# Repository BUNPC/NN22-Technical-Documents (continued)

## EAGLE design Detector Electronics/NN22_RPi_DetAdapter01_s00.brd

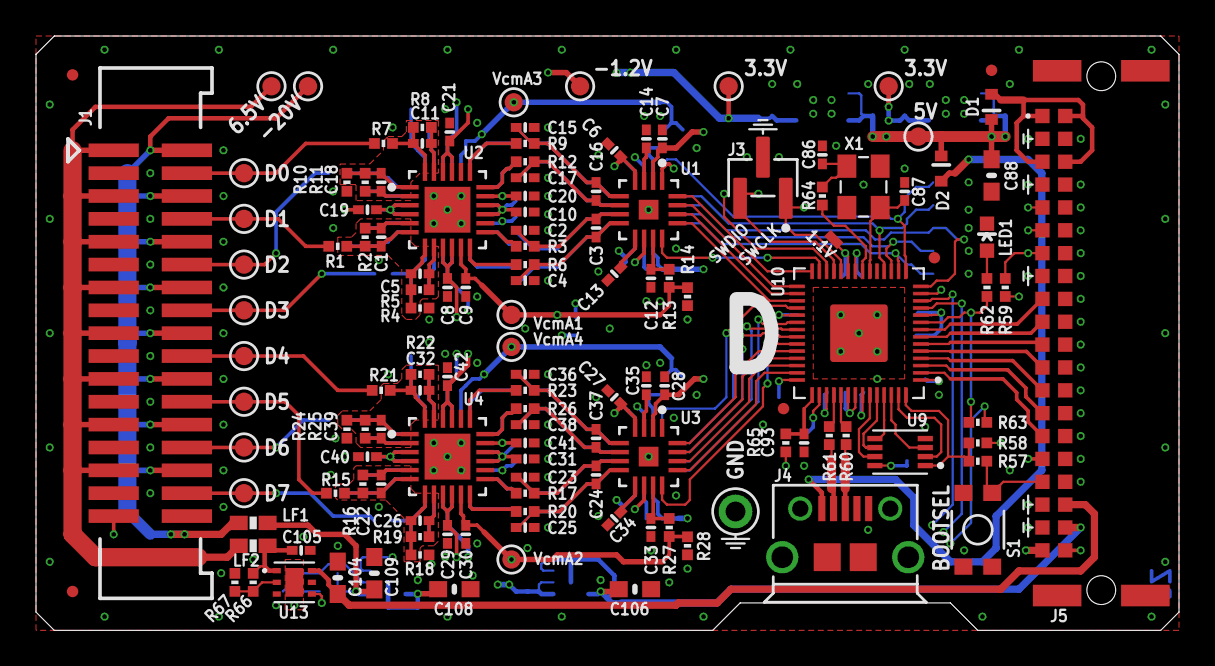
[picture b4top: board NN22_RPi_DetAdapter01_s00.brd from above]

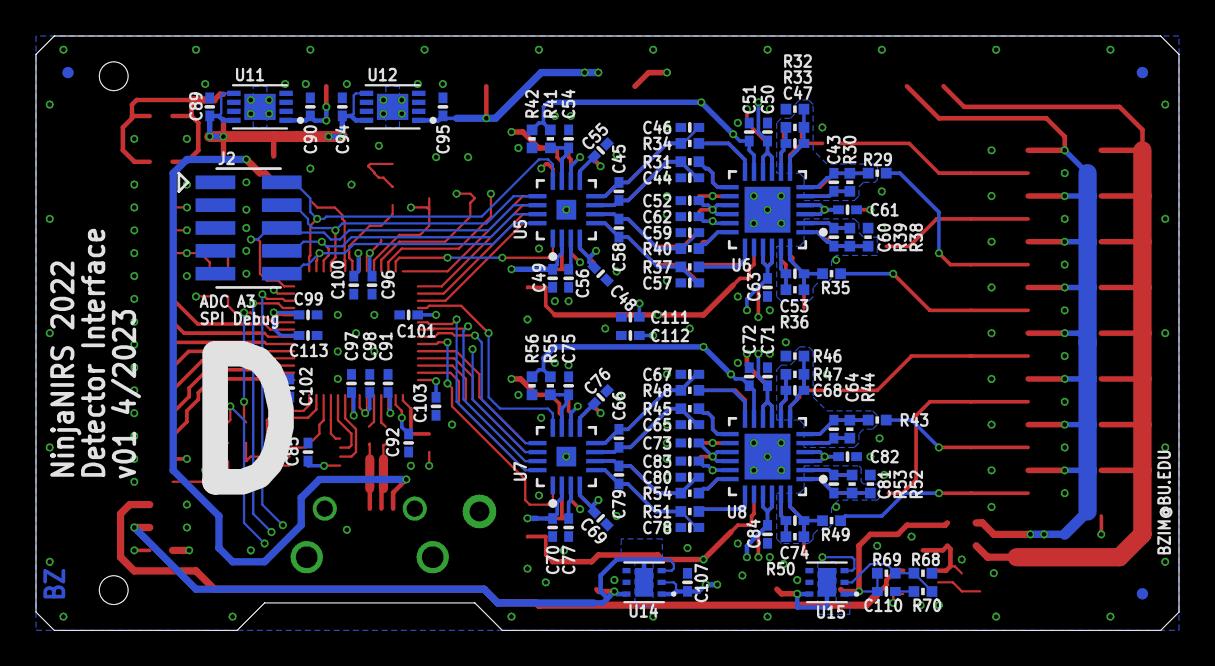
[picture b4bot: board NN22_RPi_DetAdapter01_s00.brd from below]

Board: 6 copper layers, 63.5 x 33.0 mm, 238 parts (105 on the bottom side), 156 nets.

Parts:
C1, C5, C11, C18, C22, C26, C32, C39, C43, C47, C53, C60, C64, C68, C74, C81: 330p; 0402-CAP
C2, C3, C4, C15, C16, C17, C23, C24, C25, C36, C37, C38, C44, C45, C46, C57, C58, C59, C65, C66, C67, C78, C79, C80: 1n; 0402-CAP
C6, C7, C12, C14, C27, C28, C33, C35, C48, C49, C54, C56, C69, C70, C75, C77: 1u; 0402-CAP
C8, C9, C10, C13, C19, C20, C21, C29, C30, C31, C34, C40, C41, C42, C50, C51, C52, C55, C61, C62, C63, C71, C72, C73, C76, C82, C83, C84, C85, C96, C97, C98, C99, C100, C101, C102, C103: 0.1u; 0402-CAP
C86, C87: 27p; 0402-CAP
C88, C104, C106, C108, C109: 10u; 0603-CAP
C89, C90, C91, C92, C93, C94, C95, C105, C107, C111, C112, C113: 4.7u; 0402-CAP
C110: 33n; 0402-CAP
D1, D2: SBR1A20T5; SOD523
FID1, FID2, FID3, FID4, FID5, FID6, FID7, FID8: FIDUCIALUFIDUCIAL; MICRO-FIDUCIAL
J1: M17X2; M17X2_0.050_SHF
J2: M05X2_SMD_0.050_NOCREAM; M05X2_0.050_SMD_NO_CREAM
J3: M03X1_0.050_SMD_NO_CREAM
J4: USB-MICRO
J5: M20X2_HARFLEX_M
LED1: LED-0603
LF1, LF2: FERRITE0603; 0603-FER
R1, R4, R7, R10, R13, R14, R15, R18, R21, R24, R27, R28, R29, R32, R35, R38, R41, R42, R43, R46, R49, R52, R55, R56: 18k; 0402-RES
R2, R5, R8, R11, R16, R19, R22, R25, R30, R33, R36, R39, R44, R47, R50, R53: 2.2k; 0402-RES
R3, R6, R9, R12, R17, R20, R23, R26, R31, R34, R37, R40, R45, R48, R51, R54, R65: 33; 0402-RES
R57, R62, R64: 1.2k; 0402-RES
R58, R59, R67: 100k; 0402-RES
R60, R61: 27; 0402-RES
R63: DNP; 0402-RES
R66: 30k; 0402-RES
R68, R70: 10k; 0402-RES
R69: 154k; 0402-RES
S1: SWITCH-MOMENTARY-2SMD-3; TACTILE_SWITCH_SMD-3
TP1, TP2, TP3, TP4, TP5, TP6, TP7, TP8, TP9, TP11, TP12, TP13, TP15, TP16, TP17, TP18, TP19, TP22: TESTPOINT_ROUND; TESTPAD_ROUND
TP20: TESTPOINT1X01; 1X01
TP21: TESTPOINTPADSMALL; TESTPAD_SMALL
U1, U3, U5, U7: AD7380; LFCSP16
U2, U4, U6, U8: ADA4940-2; LFCSP24
U9: W25Q_USON; USON8L-2X3MM
U10: RP2040; QFN-56_EP
U11, U12: MCP1755_DFN; DFN8_2X3MM
U13: ADP7142_WSON; WSON6
U14, U15: ADP7182_WSON; WSON6
X1: CRYSTAL-3.2-2.5

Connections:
/CS_A1: U1.12, U10.27
/CS_A2: U3.12, U10.37
/CS_A3: J2.2, U5.12, U10.15
/CS_A4: U7.12, U10.32
A_COMM: J1.33, R63.2
BOOTSEL: J5.B17, R57.1, S1.4
DET0: J1.4, R7.1, TP4.P$1
DET1: J1.8, R1.1, TP1.P$1
DET2: J1.12, R29.1, TP9.P$1
DET3: J1.16, R35.1, TP11.P$1
DET4: J1.20, R21.1, TP7.P$1
DET5: J1.24, R15.1, TP6.P$1
DET6: J1.28, R43.1, TP13.P$1
DET7: J1.32, R49.1, TP15.P$1
GND: C2.1, C4.2, C6.2, C7.2, C8.2, C9.2, C10.2, C12.2, C13.2, C14.2, C15.1, C17.2, C19.2, C20.2, C21.2, C23.1, C25.2, C27.2, C28.2, C29.2, C30.2, C31.2, C33.2, C34.2, C35.2, C36.1, C38.2, C40.2, C41.2, C42.2, C44.1, C46.2, C48.2, C49.2, C50.2, C51.2, C52.2, C54.2, C55.2, C56.2, C57.1, C59.2, C61.2, C62.2, C63.2, C65.1, C67.2, C69.2, C70.2, C71.2, C72.2, C73.2, C75.2, C76.2, C77.2, C78.1, C80.2, C82.2, C83.2, C84.2, C85.2, C86.2, C87.2, C88.2, C89.2, C90.2, C91.2, C92.2, C93.2, C94.2, C95.2, C96.2, C97.2, C98.2, C99.2, C100.2, C101.2, C102.2, C103.2, C104.2, C105.2, C106.1, C107.1, C108.1, C109.1, C111.2, C112.1, C113.2, J1.3, J1.7, J1.11, J1.15, J1.19, J1.23, J1.27, J1.31, J2.1, J2.3, J2.5, J2.7, J2.9, J3.2, J4.5, J4.SH1, J4.SH2, J4.SH3, J4.SH4, J4.SH5, J4.SH6, J5.A2, J5.A4, J5.A5, J5.A6, J5.A7, J5.A8, J5.A9, J5.A10, J5.A11, J5.A12, J5.A13, J5.A14, J5.A15, J5.A16, J5.A17, J5.A20, J5.B2, J5.B4, J5.B8, J5.B18, J5.B19, LED1.C, R4.1, R10.1, R14.1, R18.1, R24.1, R28.1, R32.1, R38.1, R42.1, R46.1, R52.1, R56.1, R67.1, R68.2, S1.1, TP20.1, U1.1, U1.10, U1.EP, U2.EP, U3.1, U3.10, U3.EP, U4.EP, U5.1, U5.10, U5.EP, U6.EP, U7.1, U7.10, U7.EP, U8.EP, U9.4, U10.19, U10.PAD, U11.4, U11.P, U12.4, U12.P, U13.3, U13.PAD, U14.5, U15.5, X1.2, X1.4
GPIO00: J5.B15, U10.2
GPIO01: J5.B14, U10.3
GPIO02: J5.B13, U10.4
GPIO03: J5.B12, U10.5
GPIO04: J5.B11, U10.6
GPIO05: J5.B10, U10.7
GPIO06: J5.B9, U10.8
LED: R62.2, R63.1, U10.9
unnamed: R3.1, U2.13
unnamed: R6.1, U2.12
unnamed: C2.2, C3.1, R3.2, U1.7
unnamed: C3.2, C4.1, R6.2, U1.8
unnamed: C11.2, R8.2, U2.23
unnamed: C12.1, R13.2, U1.11
unnamed: C13.1, U1.9
unnamed: C14.1, U1.3
unnamed: C18.2, R11.2, U2.2
unnamed: R17.1, U4.13
unnamed: R9.1, U2.19
unnamed: R12.1, U2.18
unnamed: C15.2, C16.1, R9.2, U1.5
unnamed: C16.2, C17.1, R12.2, U1.6
unnamed: R20.1, U4.12
unnamed: C87.1, U10.20, X1.3
unnamed: C86.1, R64.2, X1.1
unnamed: R64.1, U10.21
unnamed: C1.1, R1.2, R2.1, U2.6
unnamed: C1.2, R2.2, U2.5
unnamed: C5.2, R5.2, U2.8
unnamed: C5.1, R4.2, R5.1, U2.7
unnamed: C11.1, R7.2, R8.1, U2.24
unnamed: C18.1, R10.2, R11.1, U2.1
unnamed: C23.2, C24.1, R17.2, U3.7
unnamed: C24.2, C25.1, R20.2, U3.8
unnamed: R68.1, R69.2, R70.2, U15.2
unnamed: R66.1, R67.2, U13.2
unnamed: R60.1, U10.47
unnamed: R61.1, U10.46
unnamed: C33.1, R27.2, U3.11
unnamed: C34.1, U3.9
unnamed: C35.1, U3.3
unnamed: J4.2, R61.2
unnamed: J4.3, R60.2
unnamed: R23.1, U4.19
unnamed: R26.1, U4.18
unnamed: C36.2, C37.1, R23.2, U3.5
unnamed: C37.2, C38.1, R26.2, U3.6
unnamed: C93.1, R65.2, U10.43
unnamed: C22.1, R15.2, R16.1, U4.6
unnamed: C22.2, R16.2, U4.5
unnamed: C26.2, R19.2, U4.8
unnamed: C26.1, R18.2, R19.1, U4.7
unnamed: C32.1, R21.2, R22.1, U4.24
unnamed: C39.1, R24.2, R25.1, U4.1
unnamed: C32.2, R22.2, U4.23
unnamed: C39.2, R25.2, U4.2
unnamed: R31.1, U6.13
unnamed: R34.1, U6.12
unnamed: C44.2, C45.1, R31.2, U5.7
unnamed: C45.2, C46.1, R34.2, U5.8
unnamed: C54.1, R41.2, U5.11
unnamed: C55.1, U5.9
unnamed: C56.1, U5.3
unnamed: R37.1, U6.19
unnamed: R40.1, U6.18
unnamed: C57.2, C58.1, R37.2, U5.5
unnamed: C58.2, C59.1, R40.2, U5.6
unnamed: C43.1, R29.2, R30.1, U6.6
unnamed: C43.2, R30.2, U6.5
unnamed: C47.2, R33.2, U6.8
unnamed: C47.1, R32.2, R33.1, U6.7
unnamed: C53.1, R35.2, R36.1, U6.24
unnamed: C60.1, R38.2, R39.1, U6.1
unnamed: C53.2, R36.2, U6.23
unnamed: C60.2, R39.2, U6.2
unnamed: R45.1, U8.13
unnamed: R48.1, U8.12
unnamed: C65.2, C66.1, R45.2, U7.7
unnamed: C66.2, C67.1, R48.2, U7.8
unnamed: C75.1, R55.2, U7.11
unnamed: C76.1, U7.9
unnamed: C77.1, U7.3
unnamed: R51.1, U8.19
unnamed: R54.1, U8.18
unnamed: C78.2, C79.1, R51.2, U7.5
unnamed: C79.2, C80.1, R54.2, U7.6
unnamed: C64.1, R43.2, R44.1, U8.6
unnamed: C64.2, R44.2, U8.5
unnamed: C68.2, R47.2, U8.8
unnamed: C68.1, R46.2, R47.1, U8.7
unnamed: C74.1, R49.2, R50.1, U8.24
unnamed: C81.1, R52.2, R53.1, U8.1
unnamed: C74.2, R50.2, U8.23
unnamed: C81.2, R53.2, U8.2
unnamed: C110.1, R70.1
unnamed: LED1.A, R62.1
OPT_EN_VN: U10.12, U15.3
OPT_EN_VP: U10.11, U13.4
QSPI_SCLK: U9.6, U10.52
QSPI_SD0: U9.5, U10.53
QSPI_SD1: U9.2, U10.55
QSPI_SD2: U9.3, U10.54
QSPI_SD3: U9.7, U10.51
QSPI_SS_N: R57.2, R58.1, U9.1, U10.56
RUN: J5.B7, R59.1, U10.26
SCLK_A1: U1.16, U10.28
SCLK_A2: U3.16, U10.38
SCLK_A3: J2.10, U5.16, U10.16
SCLK_A4: U7.16, U10.34
SDI_A1: U1.15, U10.29
SDI_A2: U3.15, U10.39
SDI_A3: J2.8, U5.15, U10.17
SDI_A4: U7.15, U10.35
SDOA_A1: U1.13, U10.31
SDOA_A2: U3.13, U10.41
SDOA_A3: J2.4, U5.13, U10.18
SDOA_A4: U7.13, U10.36
SDOB_A1: U1.14, U10.30
SDOB_A2: U3.14, U10.40
SDOB_A3: J2.6, U5.14, U10.14
SDOB_A4: U7.14, U10.13
SWCLK: J3.1, J5.B6, U10.24
SWDIO: J3.3, J5.B5, U10.25
V1P1: C91.1, C96.1, C97.1, TP21.P$1, U10.23, U10.45, U10.50
V3P3: C7.1, C28.1, C49.1, C70.1, C85.1, C90.1, C92.1, C98.1, C99.1, C100.1, C101.1, C102.1, C103.1, C113.1, J5.B16, R58.2, R59.2, R65.1, TP17.P$1, U1.2, U3.2, U5.2, U7.2, U9.8, U10.1, U10.10, U10.22, U10.33, U10.42, U10.44, U10.48, U10.49, U11.1
V3P3A: C6.1, C8.1, C19.1, C27.1, C29.1, C40.1, C48.1, C50.1, C61.1, C69.1, C71.1, C82.1, C95.1, C111.1, TP18.P$1, U1.4, U2.3, U2.4, U2.9, U2.10, U3.4, U4.3, U4.4, U4.9, U4.10, U5.4, U6.3, U6.4, U6.9, U6.10, U7.4, U8.3, U8.4, U8.9, U8.10, U12.1
V5P0: C88.1, C89.1, C94.1, D1.C, D2.C, TP22.P$1, U11.5, U11.8, U12.5, U12.8
V5P0_IN: D1.A, J5.A1, J5.A3, J5.B1, J5.B3
V6P5: C105.1, LF1.2, R66.2, U13.1
V6P5CON: J1.1, J1.5, J1.9, J1.13, J1.17, J1.21, J1.25, J1.29, LF1.1, TP2.P$1
V9P0: C104.1, J5.A18, U13.6
VBUS: D2.A, J4.1
VN1P2: C10.1, C21.1, C31.1, C42.1, C52.1, C63.1, C73.1, C84.1, C107.2, C112.2, TP19.P$1, U2.15, U2.16, U2.21, U2.22, U4.15, U4.16, U4.21, U4.22, U6.15, U6.16, U6.21, U6.22, U8.15, U8.16, U8.21, U8.22, U14.1, U14.2
VN3P0: C106.2, J5.A19, U14.3, U14.6, U14.PAD
VN20P0: C109.2, C110.2, LF2.2, R69.1, U15.1
VN20P0CON: J1.2, J1.6, J1.10, J1.14, J1.18, J1.22, J1.26, J1.30, LF2.1, TP3.P$1
VN22: C108.2, J5.B20, U15.6, U15.PAD
VOCM_A1: C9.1, C20.1, R13.1, R14.2, TP5.P$1, U2.11, U2.17
VOCM_A2: C30.1, C41.1, R27.1, R28.2, TP8.P$1, U4.11, U4.17
VOCM_A3: C51.1, C62.1, R41.1, R42.2, TP12.P$1, U6.11, U6.17
VOCM_A4: C72.1, C83.1, R55.1, R56.2, TP16.P$1, U8.11, U8.17

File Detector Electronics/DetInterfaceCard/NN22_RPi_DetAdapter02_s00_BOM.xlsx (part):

Designator | Value | Footprint | Populate | MPN | Manufacturer
C1 | 330p | 0402-CAP | 1 | GRM1555C1H331JA01D | Murata
C10 | 0.1u | 0402-CAP | 1 | GRM155R71H104KE14D | Murata
C100 | 0.1u | 0402-CAP | 1 | GRM155R71H104KE14D | Murata
C101 | 0.1u | 0402-CAP | 1 | GRM155R71H104KE14D | Murata
C102 | 0.1u | 0402-CAP | 1 | GRM155R71H104KE14D | Murata
C103 | 0.1u | 0402-CAP | 1 | GRM155R71H104KE14D | Murata
C104 | 10u | 0603-CAP | 1 | GRM188R6YA106MA73D | Murata
C105 | 4.7u | 0402-CAP | 1 | CL05A475MP5NRNC | Samsung
C106 | 10u | 0603-CAP | 1 | GRM188R6YA106MA73D | Murata
C107 | 4.7u | 0402-CAP | 1 | CL05A475MP5NRNC | Samsung
C108 | 10u | 0603-CAP | 1 | GRM188R6YA106MA73D | Murata
C109 | 10u | 0603-CAP | 1 | GRM188R6YA106MA73D | Murata
C11 | 330p | 0402-CAP | 1 | GRM1555C1H331JA01D | Murata
C110 | 33n | 0402-CAP | 1 | GCM155R71E333KA55D | Murata
C111 | 4.7u | 0402-CAP | 1 | CL05A475MP5NRNC | Samsung
C112 | 4.7u | 0402-CAP | 1 | CL05A475MP5NRNC | Samsung
C113 | 4.7u | 0402-CAP | 1 | CL05A475MP5NRNC | Samsung
C12 | 1u | 0402-CAP | 1 | CL05A105KP5NNNC | Samsung
C13 | 0.1u | 0402-CAP | 1 | GRM155R71H104KE14D | Murata
C14 | 1u | 0402-CAP | 1 | CL05A105KP5NNNC | Samsung
C15 | 1n | 0402-CAP | 1 | GRM1555C1H102JA01D | Murata
C16 | 1n | 0402-CAP | 1 | GRM1555C1H102JA01D | Murata
C17 | 1n | 0402-CAP | 1 | GRM1555C1H102JA01D | Murata
C18 | 330p | 0402-CAP | 1 | GRM1555C1H331JA01D | Murata
C19 | 0.1u | 0402-CAP | 1 | GRM155R71H104KE14D | Murata
C2 | 1n | 0402-CAP | 1 | GRM1555C1H102JA01D | Murata
C20 | 0.1u | 0402-CAP | 1 | GRM155R71H104KE14D | Murata
C21 | 0.1u | 0402-CAP | 1 | GRM155R71H104KE14D | Murata
C22 | 330p | 0402-CAP | 1 | GRM1555C1H331JA01D | Murata
C23 | 1n | 0402-CAP | 1 | GRM1555C1H102JA01D | Murata
C24 | 1n | 0402-CAP | 1 | GRM1555C1H102JA01D | Murata
C25 | 1n | 0402-CAP | 1 | GRM1555C1H102JA01D | Murata
C26 | 330p | 0402-CAP | 1 | GRM1555C1H331JA01D | Murata
C27 | 1u | 0402-CAP | 1 | CL05A105KP5NNNC | Samsung
C28 | 1u | 0402-CAP | 1 | CL05A105KP5NNNC | Samsung
C29 | 0.1u | 0402-CAP | 1 | GRM155R71H104KE14D | Murata
C3 | 1n | 0402-CAP | 1 | GRM1555C1H102JA01D | Murata
C30 | 0.1u | 0402-CAP | 1 | GRM155R71H104KE14D | Murata
C31 | 0.1u | 0402-CAP | 1 | GRM155R71H104KE14D | Murata
C32 | 330p | 0402-CAP | 1 | GRM1555C1H331JA01D | Murata
C33 | 1u | 0402-CAP | 1 | CL05A105KP5NNNC | Samsung
C34 | 0.1u | 0402-CAP | 1 | GRM155R71H104KE14D | Murata
C35 | 1u | 0402-CAP | 1 | CL05A105KP5NNNC | Samsung
C36 | 1n | 0402-CAP | 1 | GRM1555C1H102JA01D | Murata
C37 | 1n | 0402-CAP | 1 | GRM1555C1H102JA01D | Murata
C38 | 1n | 0402-CAP | 1 | GRM1555C1H102JA01D | Murata
C39 | 330p | 0402-CAP | 1 | GRM1555C1H331JA01D | Murata
C4 | 1n | 0402-CAP | 1 | GRM1555C1H102JA01D | Murata
C40 | 0.1u | 0402-CAP | 1 | GRM155R71H104KE14D | Murata
C41 | 0.1u | 0402-CAP | 1 | GRM155R71H104KE14D | Murata
C42 | 0.1u | 0402-CAP | 1 | GRM155R71H104KE14D | Murata
C43 | 330p | 0402-CAP | 1 | GRM1555C1H331JA01D | Murata
C44 | 1n | 0402-CAP | 1 | GRM1555C1H102JA01D | Murata
C45 | 1n | 0402-CAP | 1 | GRM1555C1H102JA01D | Murata
C46 | 1n | 0402-CAP | 1 | GRM1555C1H102JA01D | Murata
C47 | 330p | 0402-CAP | 1 | GRM1555C1H331JA01D | Murata
C48 | 1u | 0402-CAP | 1 | CL05A105KP5NNNC | Samsung
C49 | 1u | 0402-CAP | 1 | CL05A105KP5NNNC | Samsung
C5 | 330p | 0402-CAP | 1 | GRM1555C1H331JA01D | Murata
C50 | 0.1u | 0402-CAP | 1 | GRM155R71H104KE14D | Murata
C51 | 0.1u | 0402-CAP | 1 | GRM155R71H104KE14D | Murata
C52 | 0.1u | 0402-CAP | 1 | GRM155R71H104KE14D | Murata
C53 | 330p | 0402-CAP | 1 | GRM1555C1H331JA01D | Murata
C54 | 1u | 0402-CAP | 1 | CL05A105KP5NNNC | Samsung
C55 | 0.1u | 0402-CAP | 1 | GRM155R71H104KE14D | Murata
C56 | 1u | 0402-CAP | 1 | CL05A105KP5NNNC | Samsung
C57 | 1n | 0402-CAP | 1 | GRM1555C1H102JA01D | Murata
C58 | 1n | 0402-CAP | 1 | GRM1555C1H102JA01D | Murata
C59 | 1n | 0402-CAP | 1 | GRM1555C1H102JA01D | Murata
C6 | 1u | 0402-CAP | 1 | CL05A105KP5NNNC | Samsung
C60 | 330p | 0402-CAP | 1 | GRM1555C1H331JA01D | Murata
C61 | 0.1u | 0402-CAP | 1 | GRM155R71H104KE14D | Murata
C62 | 0.1u | 0402-CAP | 1 | GRM155R71H104KE14D | Murata
C63 | 0.1u | 0402-CAP | 1 | GRM155R71H104KE14D | Murata
C64 | 330p | 0402-CAP | 1 | GRM1555C1H331JA01D | Murata
C65 | 1n | 0402-CAP | 1 | GRM1555C1H102JA01D | Murata
C66 | 1n | 0402-CAP | 1 | GRM1555C1H102JA01D | Murata
C67 | 1n | 0402-CAP | 1 | GRM1555C1H102JA01D | Murata
C68 | 330p | 0402-CAP | 1 | GRM1555C1H331JA01D | Murata
C69 | 1u | 0402-CAP | 1 | CL05A105KP5NNNC | Samsung
C7 | 1u | 0402-CAP | 1 | CL05A105KP5NNNC | Samsung
C70 | 1u | 0402-CAP | 1 | CL05A105KP5NNNC | Samsung
C71 | 0.1u | 0402-CAP | 1 | GRM155R71H104KE14D | Murata
C72 | 0.1u | 0402-CAP | 1 | GRM155R71H104KE14D | Murata
C73 | 0.1u | 0402-CAP | 1 | GRM155R71H104KE14D | Murata
C74 | 330p | 0402-CAP | 1 | GRM1555C1H331JA01D | Murata
C75 | 1u | 0402-CAP | 1 | CL05A105KP5NNNC | Samsung
C76 | 0.1u | 0402-CAP | 1 | GRM155R71H104KE14D | Murata
C77 | 1u | 0402-CAP | 1 | CL05A105KP5NNNC | Samsung
C78 | 1n | 0402-CAP | 1 | GRM1555C1H102JA01D | Murata
C79 | 1n | 0402-CAP | 1 | GRM1555C1H102JA01D | Murata
C8 | 0.1u | 0402-CAP | 1 | GRM155R71H104KE14D | Murata
C80 | 1n | 0402-CAP | 1 | GRM1555C1H102JA01D | Murata
C81 | 330p | 0402-CAP | 1 | GRM1555C1H331JA01D | Murata
C82 | 0.1u | 0402-CAP | 1 | GRM155R71H104KE14D | Murata
C83 | 0.1u | 0402-CAP | 1 | GRM155R71H104KE14D | Murata
C84 | 0.1u | 0402-CAP | 1 | GRM155R71H104KE14D | Murata
C85 | 0.1u | 0402-CAP | 1 | GRM155R71H104KE14D | Murata
C86 | 27p | 0402-CAP | 1 | GCM1555C1H270JA16D | Murata
C87 | 27p | 0402-CAP | 1 | GCM1555C1H270JA16D | Murata
C88 | 10u | 0603-CAP | 1 | GRM188R6YA106MA73D | Murata
C89 | 4.7u | 0402-CAP | 1 | CL05A475MP5NRNC | Samsung
C9 | 0.1u | 0402-CAP | 1 | GRM155R71H104KE14D | Murata
C90 | 4.7u | 0402-CAP | 1 | CL05A475MP5NRNC | Samsung
C91 | 4.7u | 0402-CAP | 1 | CL05A475MP5NRNC | Samsung
C92 | 4.7u | 0402-CAP | 1 | CL05A475MP5NRNC | Samsung
C93 | 4.7u | 0402-CAP | 1 | CL05A475MP5NRNC | Samsung
C94 | 4.7u | 0402-CAP | 1 | CL05A475MP5NRNC | Samsung
C95 | 4.7u | 0402-CAP | 1 | CL05A475MP5NRNC | Samsung
C96 | 0.1u | 0402-CAP | 1 | GRM155R71H104KE14D | Murata
C97 | 0.1u | 0402-CAP | 1 | GRM155R71H104KE14D | Murata
C98 | 0.1u | 0402-CAP | 1 | GRM155R71H104KE14D | Murata
C99 | 0.1u | 0402-CAP | 1 | GRM155R71H104KE14D | Murata
D1 | SBR1A20T5 | SOD523 | 1 | SBR1A20T5-7 | Diodes Inc.
D2 | SBR1A20T5 | SOD523 | 1 | SBR1A20T5-7 | Diodes Inc.
FID1 | FIDUCIALUFIDUCIAL | MICRO-FIDUCIAL | 0
FID2 | FIDUCIALUFIDUCIAL | MICRO-FIDUCIAL | 0
FID3 | FIDUCIALUFIDUCIAL | MICRO-FIDUCIAL | 0
FID4 | FIDUCIALUFIDUCIAL | MICRO-FIDUCIAL | 0
FID5 | FIDUCIALUFIDUCIAL | MICRO-FIDUCIAL | 0
FID6 | FIDUCIALUFIDUCIAL | MICRO-FIDUCIAL | 0
FID7 | FIDUCIALUFIDUCIAL | MICRO-FIDUCIAL | 0
FID8 | FIDUCIALUFIDUCIAL | MICRO-FIDUCIAL | 0
J1 | M17X2 | M17X2_0.050_SHF | 1 | SHF-117-01-L-D-SM | Samtec
J2 | M05X2_SMD_0.050_NOCREAM | M05X2_0.050_SMD_NO_CREAM | 0
J3 | M03X1_0.050_SMD_NO_CREAM | M03X1_0.050_SMD_NO_CREAM | 0
J4 | USB-MICRO | USB-MICRO | 1 | 10118194-0001LF | Amphenol Communications Solutions
J5 | M20X2_HARFLEX_M | M20X2_HARFLEX_M | 1 | 15150402601000 | HARTING Elektronik
LED1 |  | LED-0603 | 1 | LTST-C191KRKT | Lite-On
LF1 | FERRITE0603 | 0603-FER | 1 | BLM18AG601SN1D | Murata
LF2 | FERRITE0603 | 0603-FER | 1 | BLM18AG601SN1D | Murata
R1 | 18k | 0402-RES | 1 | RR0510P-183-D | Susumu
R10 | 18k | 0402-RES | 1 | RR0510P-183-D | Susumu
R11 | 2.2k | 0402-RES | 1 | RR0510P-222-D | Susumu
R12 | 33 | 0402-RES | 1 | CRCW040233R0FKEDC | Vishay
R13 | 18k | 0402-RES | 1 | RR0510P-183-D | Susumu
R14 | 18k | 0402-RES | 1 | RR0510P-183-D | Susumu
R15 | 18k | 0402-RES | 1 | RR0510P-183-D | Susumu
R16 | 2.2k | 0402-RES | 1 | RR0510P-222-D | Susumu
R17 | 33 | 0402-RES | 1 | CRCW040233R0FKEDC | Vishay
R18 | 18k | 0402-RES | 1 | RR0510P-183-D | Susumu
R19 | 2.2k | 0402-RES | 1 | RR0510P-222-D | Susumu
R2 | 2.2k | 0402-RES | 1 | RR0510P-222-D | Susumu
R20 | 33 | 0402-RES | 1 | CRCW040233R0FKEDC | Vishay
R21 | 18k | 0402-RES | 1 | RR0510P-183-D | Susumu
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
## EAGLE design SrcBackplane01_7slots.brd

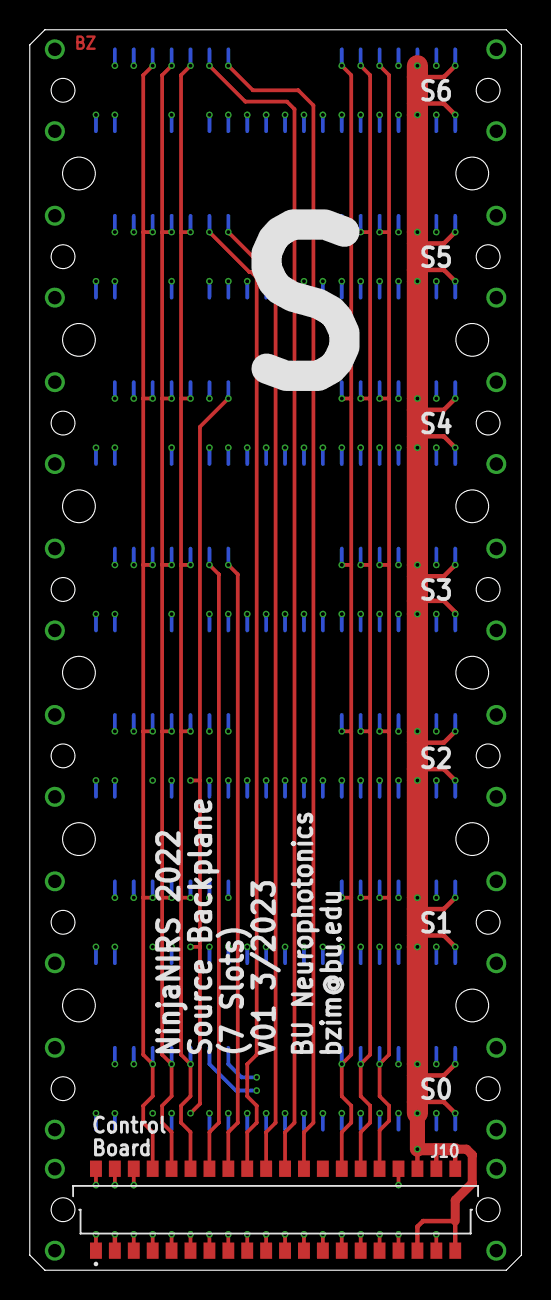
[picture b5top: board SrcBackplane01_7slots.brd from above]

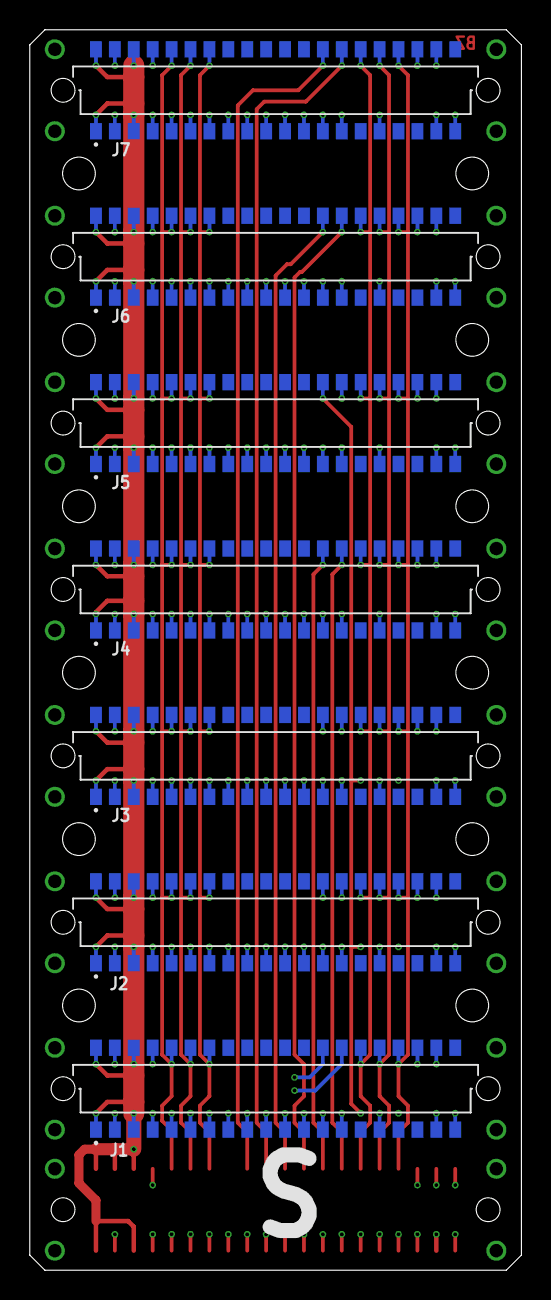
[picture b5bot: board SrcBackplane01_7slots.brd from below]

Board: 4 copper layers, 33.0 x 83.3 mm, 8 parts (7 on the bottom side), 23 nets.

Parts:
J1, J2, J3, J4, J5, J6, J7, J10: M20X2_STR_MPTH; M20X2_HARFLEX_F_STR_MPTH

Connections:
COL00: J1.B13, J10.A11
COL01: J1.B14, J10.A10
COL02: J2.B13, J10.A8
COL03: J2.B14, J10.A7
COL04: J3.B13, J10.A6
COL05: J3.B14, J10.A5
COL06: J4.B13, J10.B8
COL07: J4.B14, J10.B7
COL08: J5.B13, J10.A4
COL09: J5.B14, J10.A3
COL10: J6.B13, J10.B10
COL11: J6.B14, J10.B9
COL12: J7.B13, J10.B12
COL13: J7.B14, J10.B11
GND: J1.A2, J1.A4, J1.A5, J1.A6, J1.A7, J1.A8, J1.A9, J1.A10, J1.A11, J1.A12, J1.A13, J1.A14, J1.A16, J1.A20, J1.B2, J1.B4, J1.B18, J1.B19, J2.A2, J2.A4, J2.A5, J2.A6, J2.A7, J2.A8, J2.A9, J2.A10, J2.A11, J2.A12, J2.A13, J2.A14, J2.A16, J2.A20, J2.B2, J2.B4, J2.B18, J2.B19, J3.A2, J3.A4, J3.A5, J3.A6, J3.A7, J3.A8, J3.A9, J3.A10, J3.A11, J3.A12, J3.A13, J3.A14, J3.A16, J3.A20, J3.B2, J3.B4, J3.B18, J3.B19, J4.A2, J4.A4, J4.A5, J4.A6, J4.A7, J4.A8, J4.A9, J4.A10, J4.A11, J4.A12, J4.A13, J4.A14, J4.A16, J4.A20, J4.B2, J4.B4, J4.B18, J4.B19, J5.A2, J5.A4, J5.A5, J5.A6, J5.A7, J5.A8, J5.A9, J5.A10, J5.A11, J5.A12, J5.A13, J5.A14, J5.A16, J5.A20, J5.B2, J5.B4, J5.B18, J5.B19, J6.A2, J6.A4, J6.A5, J6.A6, J6.A7, J6.A8, J6.A9, J6.A10, J6.A11, J6.A12, J6.A13, J6.A14, J6.A16, J6.A20, J6.B2, J6.B4, J6.B18, J6.B19, J7.A2, J7.A4, J7.A5, J7.A6, J7.A7, J7.A8, J7.A9, J7.A10, J7.A11, J7.A12, J7.A13, J7.A14, J7.A16, J7.A20, J7.B2, J7.B4, J7.B18, J7.B19, J10.A1, J10.A9, J10.A12, J10.A13, J10.A14, J10.A15, J10.A16, J10.A17, J10.A19, J10.B1, J10.B2, J10.B3, J10.B17
PWR0: J1.B15, J2.B15, J3.B15, J4.B15, J5.B15, J6.B15, J7.B15, J10.B6
PWR1: J1.B16, J2.B16, J3.B16, J4.B16, J5.B16, J6.B16, J7.B16, J10.B5
PWR2: J1.B17, J2.B17, J3.B17, J4.B17, J5.B17, J6.B17, J7.B17, J10.B4
ROW0: J1.B5, J2.B5, J3.B5, J4.B5, J5.B5, J6.B5, J7.B5, J10.B16
ROW1: J1.B6, J2.B6, J3.B6, J4.B6, J5.B6, J6.B6, J7.B6, J10.B15
ROW2: J1.B7, J2.B7, J3.B7, J4.B7, J5.B7, J6.B7, J7.B7, J10.B14
V5P1: J1.A1, J1.A3, J1.B1, J1.B3, J2.A1, J2.A3, J2.B1, J2.B3, J3.A1, J3.A3, J3.B1, J3.B3, J4.A1, J4.A3, J4.B1, J4.B3, J5.A1, J5.A3, J5.B1, J5.B3, J6.A1, J6.A3, J6.B1, J6.B3, J7.A1, J7.A3, J7.B1, J7.B3, J10.A18, J10.A20, J10.B18, J10.B19, J10.B20
VN3P4: J1.A19, J2.A19, J3.A19, J4.A19, J5.A19, J6.A19, J7.A19, J10.A2

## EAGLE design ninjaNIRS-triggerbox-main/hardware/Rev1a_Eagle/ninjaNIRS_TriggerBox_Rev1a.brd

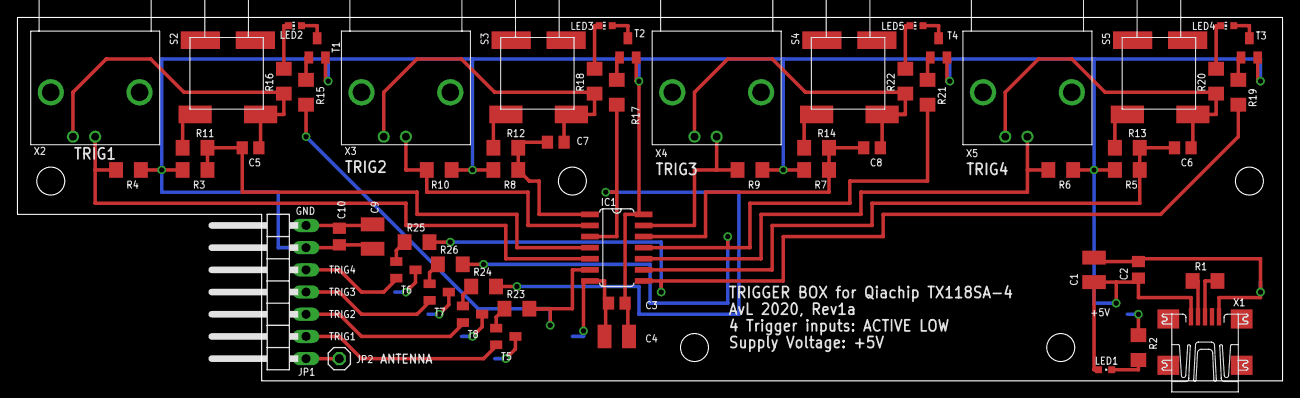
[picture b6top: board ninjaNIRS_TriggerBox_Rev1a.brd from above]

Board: 2 copper layers, 144.8 x 41.6 mm, 61 parts (0 on the bottom side), 42 nets.

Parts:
C1, C4, C9: 10uF; C1210
C2, C3, C10: 100nF; C0805
C5, C6, C7, C8: 47n; C0805
IC1: SN74HCS08-Q1; SO14
JP1: CONN RCPT 7POS 0.1" GOLD PCB R/A; 1X07/90
JP2: Antenna; 1X01
LED1: LTST-C191KGKT; CHIPLED_0603
LED2, LED3, LED4, LED5: Kingbright APA1606QBC/D; CHIP-LED0603
R1, R16, R18, R20, R22: 100; R1206
R2, R15, R17, R19, R21, R23, R24, R25, R26: 1k; R1206
R3, R4, R5, R6, R7, R8, R9, R10: 10k; R1206
R11, R12, R13, R14: 39; R1206
S2, S3, S4, S5: E-SWITCH-800BWSP9SM6RE; E-SWITCH_800BW
T1, T2, T3, T4, T5, T6, T7, T8: PNP MMBT3906; SOT23-BEC
X1: MINI-USB-UX60A-MB-5ST; UX60A-MB-5ST
X2, X3, X4, X5: TE_CON_BNC_5227161-9

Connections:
+5V: C1.1, C2.1, C3.1, C4.1, C9.1, C10.1, IC1.14, JP1.6, LED1.A, R3.2, R4.1, R5.2, R6.1, R7.2, R8.2, R9.1, R10.1, T1.E, T2.E, T3.E, T4.E, X1.1
GND: C1.2, C2.2, C3.2, C4.2, C5.1, C6.1, C7.1, C8.1, C9.2, C10.2, IC1.7, JP1.7, R2.1, R16.1, R18.1, R20.1, R22.1, S2.P$2, S3.P$2, S4.P$2, S5.P$2, T5.C, T6.C, T7.C, T8.C, X1.5, X2.P$3, X3.P$3, X4.P$3, X5.P$3
K1: JP1.2, T5.E
K1S: IC1.6, R15.1, R23.2
K2: JP1.3, T8.E
K2S: IC1.3, R17.1, R24.2
K3: JP1.4, T7.E
K3S: IC1.11, R21.1, R26.2
K4: JP1.5, T6.E
K4S: IC1.8, R19.1, R25.2
unnamed: R1.1, X1.2
unnamed: R1.2, X1.3
unnamed: IC1.5, R4.2, X2.P$4
unnamed: C5.2, IC1.4, R3.1, R11.1
unnamed: IC1.10, R6.2, X5.P$4
unnamed: IC1.2, R10.2, X3.P$4
unnamed: IC1.13, R9.2, X4.P$4
unnamed: C6.2, IC1.9, R5.1, R13.1
unnamed: C7.2, IC1.1, R8.1, R12.1
unnamed: R12.2, S3.P$1
unnamed: R14.2, S4.P$1
unnamed: R13.2, S5.P$1
unnamed: LED1.C, R2.2
unnamed: R11.2, S2.P$1
unnamed: C8.2, IC1.12, R7.1, R14.1
unnamed: R15.2, T1.B
unnamed: LED2.A, T1.C
unnamed: LED2.C, R16.2
unnamed: R17.2, T2.B
unnamed: LED3.A, T2.C
unnamed: LED3.C, R18.2
unnamed: R19.2, T3.B
unnamed: LED4.A, T3.C
unnamed: LED4.C, R20.2
unnamed: R21.2, T4.B
unnamed: LED5.A, T4.C
unnamed: LED5.C, R22.2
unnamed: R23.1, T5.B
unnamed: R25.1, T6.B
unnamed: R26.1, T7.B
unnamed: JP1.1, JP2.1
unnamed: R24.1, T8.B

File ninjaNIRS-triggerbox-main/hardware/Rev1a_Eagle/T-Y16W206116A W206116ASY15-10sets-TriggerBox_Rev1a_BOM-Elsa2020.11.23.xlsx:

|  |  | ninjaNIRS_TriggerBox_Rev1a
Item # | *Designator | *Qty | Manufacturer | *Mfg Part # | Description / Value | *Package/Footprint | Type | Your Instructions / Notes | Unit Price 10sets | Total Price | Note
1 | R1, R16, R18, R20, R22 | 5 | Yageo | RC1206FR-07100RL | RES SMD 100 OHM 1% 1/4W 1206 | 1206 | SMD |  | 2.1999999999999999E-2 | 1.0999999999999999
2 | C2, C3, C10 | 3 | Kemet | C0805C104M3RACTU | CAP CER 0.1UF 25V X7R 0805 | 0805 | SMD |  | 2.1999999999999999E-2 | 0.65999999999999992
3 | R3, R4, R5, R6, R7, R8, R9, R10 | 8 | Yageo | RC1206JR-0710KL | RES SMD 10K OHM 5% 1/4W 1206 | 1206 | SMD |  | 2.1999999999999999E-2 | 1.7599999999999998
4 | C1, C4, C9 | 3 | Samsung | CL32B106KOULNNE | CAP CER 10UF 16V X7R 1210 | 1206 | SMD |  | 0.14099999999999999 | 4.2299999999999995 | According to part number, correct package is 1210, not 1206, ok? | OK
5 | R2, R15, R17, R19, R21, R23, R24, R25, R26 | 9 | Yageo | RC1206JR-071KL | RES SMD 1K OHM 5% 1/4W 1206 | 1206 | SMD |  | 2.1999999999999999E-2 | 1.9799999999999998
6 | R11, R12, R13, R14 | 4 | Stackpole | RMCF1206FT39R0 | RES 39 OHM 1% 1/4W 1206 | 1206 | SMD |  | 2.1999999999999999E-2 | 0.87999999999999989
7 | C5, C6, C7, C8 | 4 | Kemet | C0805C473K3RACTU | CAP CER 0.047UF 25V X7R 0805 | 1206 | SMD |  | 4.2999999999999997E-2 | 1.7199999999999998 | According to part number, correct package is 0805, not 1206, OK? | OK
8 | JP2 | 0 |  |  | Antenna |  |  | DNP |  | 0 | DNP
9 | JP1 | 1 | Mill-Max | 801-43-007-20-001000 | CONN RCPT 7POS 0.1 GOLD PCB R/A |  | PTH |  |  |  | Not available, out of stock. Plz recommend replacements. | Please use Sullins PPTC071LGBN-RC
10 | S2, S3, S4, S5 | 4 | E-switch | 800BWSP9SM6RE | SWITCH PUSH SPST-NO 0.4VA 20V |  | SMD |  | 6.3860000000000001 | 255.44 | 7-10work days | How come it is this expensive? Price at Digikey is $4.14
11 | LED2, LED3, LED4, LED5 | 4 | Kingbright | APA1606QBC/D | LED BLUE CLEAR CHIP SMD R/A |  | SMD |  | 0.42399999999999999 | 16.96 | 5-7work days
12 | LED1 | 1 | Lite-on | LTST-C191KGKT | LED GREEN CLEAR SMD | 0603 | SMD |  | 0.08 | 0.8
13 | X1 | 1 | Hirose | UX60A-MB-5ST | CONN RCPT USB2.0 MINI B SMD R/A |  | SMD |  | 1.2470000000000001 | 12.47
14 | T1, T2, T3, T4, T5, T6, T7, T8 | 8 | Diodes | MMBT3906-7-F | TRANS PNP 40V 0.2A SOT23-3 | SOT 23-3 | SMD |  | 3.6999999999999998E-2 | 2.96
15 | IC1 | 1 | Texas Instruments | SN74HCS08QDRQ1 | IC LOGIC GATE | SO-14 | SMD |  | 0.50700000000000001 | 5.07 | 5-7work days
16 | X2, X3, X4, X5 | 4 | TE Connectivity | 5227161-9 | CONN BNC JACK R/A 50 OHM PCB |  | PTH |  | 4.2619999999999996 | 170.48 | 5-7work days | How come it is this expensive? Price at Digikey is $3.18
 |  |  |  |  |  |  |  |  |  | 476.51
Need a quick and accurante quote? Need an efficient production? Please read SMT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
Click for Instructions on How to Create a BOM
 |  |  |  |  |  |  |  |  | we quoted according to the list of *Mfg Part #, all OK? |  |  | OK
